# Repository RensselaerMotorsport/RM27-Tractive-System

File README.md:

# RM27-TRACTIVE-SYSTEM

NOTICE!!!
This repo is OUTDATED! The current tractive system repository is at https://github.com/RensselaerMotorsport/RM28-Tractive-System
Almost all circuits from this repo were updated for the RM28 car (FSAE 2024 competition car)

This respository currently contains one major project:
* WIP RM27 Project - This project is the most up-to-date version of the 2023-2024 competition car's High Voltage System.

To open and work with these files, specific software packages must be used.
* LTSpice - Circuit simulation software used for preliminary mockups of circuit designs. The .asc files can be opened in other spice programs like ngspice or pspice, but these circuits were originally drafted in LTSpice
* KiCad - PCB design software used for creating schematics for manufacturing.

Acronyms Used:
* ESF - Elecrtrical Systems Form
* GLV - Grounded Low Voltage
* HV - High Voltage
* TSAL - Tractive System Active Light

Typical Circuits:
* Tractive System Active Light (TSAL) - When GLV is on and HV (typically between 12-400V) is less than 60V outside the container, turns an LED green. If HV is greater than 60V, a red LED blinks at low frequency. PS16-051 is the transformer used in this circuit, but has been since discontinued. A similar transformer may need to be selected.
* Accumulator Indicator - Turns on blue LED if voltage outside the container is greater than 60V. Must work in absence of GLV.
* ESF - Shows overall design of racecar electrical system. Includes datasheets, circuit diagrams, electrical architecture, and part numbers.

Additional Circuits in this repo:
The soldering demo board for the Mercer XLab was included to be used as an instructional tool to teach other students at RPI how to solder. Several PCBs were printed and the Rensselaer Motorsport club ran a soldering workshop in the XLab. The board is a simple multivibrator that uses a potentiometer to adjust the blinking frequency of an LED. This workshop was quite successful for our lab, however keep in mind if you run a workshop with this circuit, we designed this circuit to be used with a 3V button cell battery (CR2025). Make sure that a 555 timer designed to have a 3V power rail us used so the timer works sufficiently. (We used the TLC555CP).

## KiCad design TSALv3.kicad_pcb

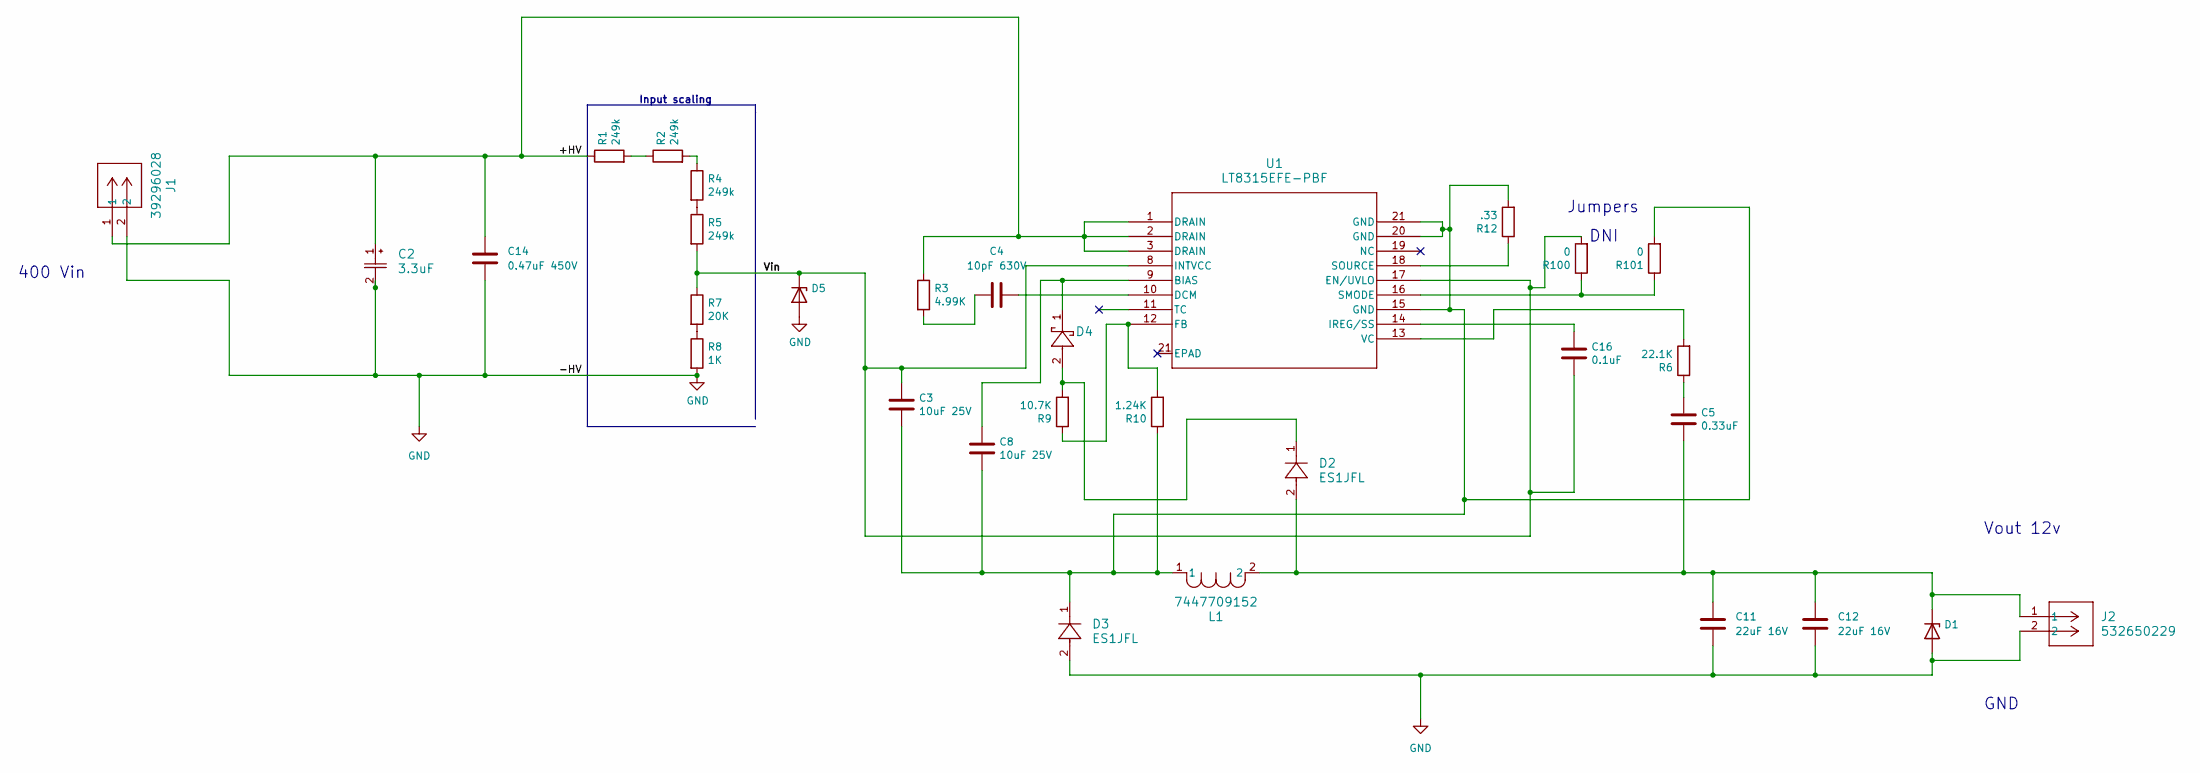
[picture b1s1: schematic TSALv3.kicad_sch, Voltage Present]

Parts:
C2: 3.3uF; CAP_ULH_8X10_NCH
C3: 10uF 25V; C_0603_1608Metric_Pad1.08x0.95mm_HandSolder
C4: 10pF 630V; C_1206_3216Metric
C5: 0.33uF; C_0603_1608Metric_Pad1.08x0.95mm_HandSolder
C8: 10uF 25V; C_1206_3216Metric_Pad1.33x1.80mm_HandSolder
C11, C12: 22uF 16V; C_1210_3225Metric_Pad1.33x2.70mm_HandSolder
C14: 0.47uF 450V; C_1812_4532Metric
C16: 0.1uF; C_0603_1608Metric_Pad1.08x0.95mm_HandSolder
D1, D5: D_SMB
D2, D3: ES1JFL; SOD-123FL_425AD_OSI
D4: CMDSH2-3 TR PBFREE; SDO_CMDSH2-3 TR PBFREE_CNS
J1: 39296028; CON_39296028
J2: 532650229; CON_532650229_MOL
L1: 7447709152; IND_1210-WE-PD_WRE
R1, R2, R4, R5: 249k; RC1210N_VIS
R3: 4.99K; R_1206_3216Metric
R6: 22.1K; R_0603_1608Metric_Pad0.98x0.95mm_HandSolder
R7: 20K; RC1210N_VIS
R8: 1K; RC1210N_VIS
R9: 10.7K; R_0201_0603Metric_Pad0.64x0.40mm_HandSolder
R10: 1.24K; R_0603_1608Metric_Pad0.98x0.95mm_HandSolder
R12: .33; R_0603_1608Metric
R100, R101: 0; R_0603_1608Metric
U1: LT8315EFE-PBF; FE_20_ADI-L

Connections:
/+HV: C2.1, C14.1, J1.1, R1.1, R3.1, U1.1 (DRAIN), U1.2 (DRAIN), U1.3 (DRAIN)
/Vin: C3.1, C16.2, D5.1 (K), R5.2, R7.1, R100.2, U1.8 (INTVCC), U1.17 (EN/UVLO)
GND: C2.2, C11.2, C12.2, C14.2, D1.2 (A), D3.2, D5.2 (A), J1.2, J2.2, R8.2
unnamed: C3.2, C8.2, D3.1, L1.1, R10.1, R12.2, R101.2, U1.15 (GND), U1.20 (GND), U1.21 (GND)
unnamed: C4.2, R3.2
unnamed: C5.1, R6.1
unnamed: C5.2, C11.1, C12.1, D1.1 (K), D2.2, J2.1, L1.2
unnamed: D2.1, D4.2, R9.2
unnamed: R1.2, R2.1
unnamed: R2.2, R4.1
unnamed: R4.2, R5.1
unnamed: R7.2, R8.1
unnamed: C8.1, D4.1, U1.9 (BIAS)
unnamed: C4.1, U1.10 (DCM)
unnamed: R9.1, R10.2, U1.12 (FB)
unnamed: C16.1, U1.14 (IREG/SS)
unnamed: R100.1, R101.1, U1.16 (SMODE)
unnamed: R12.1, U1.18 (SOURCE)
unnamed: R6.2, U1.13 (VC)

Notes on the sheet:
Input scaling
DNI
Vout 12v
Jumpers
400 Vin
GND

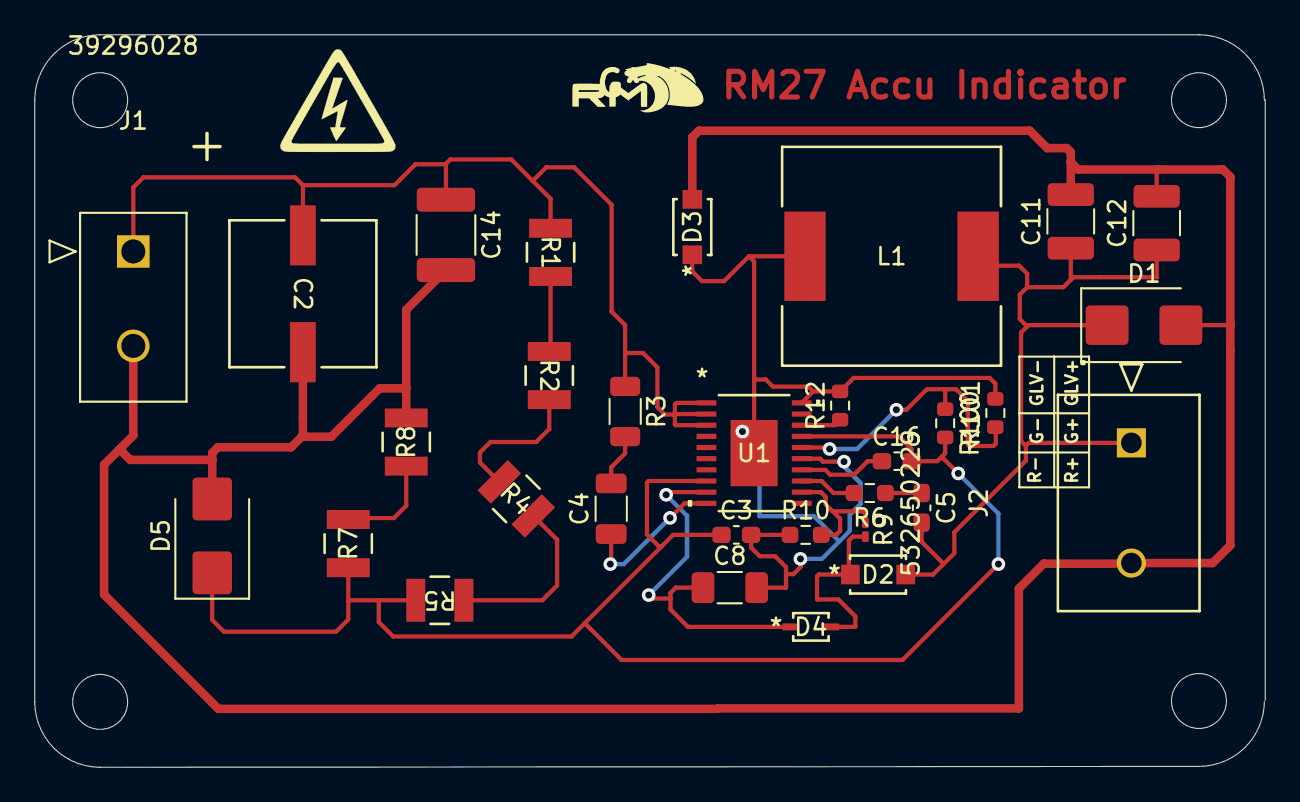
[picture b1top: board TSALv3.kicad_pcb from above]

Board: 2 copper layers, 71.7 x 42.7 mm, 35 parts (0 on the bottom side), 19 nets.

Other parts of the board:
MH1, MH2, MH3, MH4: MountingHole_3.2mm_M3

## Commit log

2024-01-30 WIP TSAL
    Adding WIP TSAL which has TSAL and voltage indicator. Transformer is messed up
2024-02-06 RM27 ESF 2.0
    Added better resolution pictures, updated TSAL schematic, and updated HV component locations
2024-02-06 Swap 12V comparators LT1441 with LM393
2024-02-06 Update README.md
    initial update
2024-02-09 Increase comparator terminal resistances to increase stability
2024-02-09 TSAL BOM
    Bill of materials for RM27 TSAL circuit
2024-02-16 Accumulator Indicator 1st draft
2024-02-16 Edit diode types and placement
2024-02-16 Initial Manufacturing Plan for RM27 Accumulator
    RM27 version of manufacturing plan
2024-02-16 RMS Software Zip
    Zip folder containing file structure for inverter setup
2024-02-23 ESF V3
    Third version of RM27 ESF. Updated schematics, datatsheets, and pictures + CAD
2024-02-23 RM27 Accumulator Tractive System Schematic
    Updated TS schematic showing all connectors, updated hardware locations, and additional circuitry such as fuses for the IMD.
2024-02-23 Use easily available (LT1011) comparators, fix some annotations on schematic
2024-02-27 RM27 Charging Shutdown Circuit
    Updated charging shutdown circuit to reflect design changes in accumulator.
2024-03-01 Fix minor wiring errors in 555 timer
2024-03-01 Decrease output resistance so LED can activate
2024-03-01 BOM for Mercer Demo Board
    All part numbers, links, etc.
2024-03-12 RM27 Accumulator Manufacturing Doc
    Shows how to assemble the accumulator segments. For reference only with pictures.
2024-03-12 Generate BMS Wiring Diagram
    This was generated on https://www.orionbms.com/tools/wiring.php?cell_count=95&fuse_position%5B%5D=20&fuse_position%5B%5D=39&fuse_position%5B%5D=58&fuse_position%5B%5D=77.
    There are 19 cells in each row of the accumulator, so halfway through the middle group, the cells are all tied to the cell that is a multiple of 19. In the left group, they are all listed as N/A beca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
2024-03-15 Accumulator Indicator Initial Schematic
    initial draft. turns on if TS voltage is greater than 60V. Runs completely off of accumulator voltage and is attached to the AIRs.
2024-03-15 TSAL mating connectors (LV + HV)
    Picture showing mating connectors for TSAL board. These are the connectors which go on the GLV and HV wiring harnesses to plug into the TSAL board. Parts are available on Digikey
2024-03-19 Add a draft for a simulation friendly version of the indicator
2024-03-19 Indicator Light
    Revised layout of indicator light. Vias added
2024-03-22 HVPS Briefing Slides
    HVPS slides for using the DANA HVPS
2024-03-29 Accu Indicator V3
    Added logo, final design changes. Pending HV/LV Spacing
2024-03-29 RM KiCad Logo
    Logo for KiCad PCB files
2024-04-05 Redraw the Demo Board Schematic so it's more readable
2024-04-05 Accumulator Indicator V1 Gerber Files
    Gerber and drill files to print PCB for accumulator indicator
2024-04-05 Add spec sheet with input/output limits and performance info for CAN bus charger
2024-04-05 RM27 TSAL Gerbers
    Drill and Gerber files for RM27 final TSAL
2024-04-11 Updated new maintenance plugs for mr trimper
2024-04-12 Accumulator Indicator with new silkscreen
    Updated silkscreen to have proper labeling and got rid of residual labels
2024-04-12 Update README.md with description of soldering board
2024-04-12 Accumulator Indicator BOM
    BOM with part #s and # of parts for accumulator indicator
2024-04-12 Clean up schematic (V2) and add accurate component labels
2024-04-16 RM27 ESF V4
    Final iteration of RM27 ESF
2024-11-30 Add link to RM28 repo in README.md
